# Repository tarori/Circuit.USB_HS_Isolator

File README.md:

USB 2.0 HS (480Mbps) 対応のUSBアイソレータ
* USB Type-C入力、Type-A出力
* アイソレータIC: ISOUSB211
* SN6505による低ノイズ絶縁DCDC
* 絶縁容量: <5pF (トランス次第)

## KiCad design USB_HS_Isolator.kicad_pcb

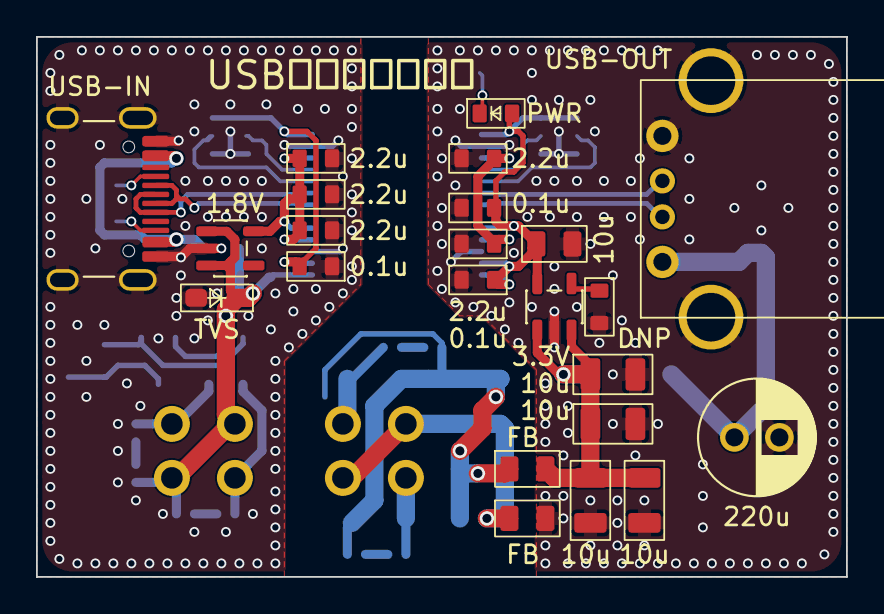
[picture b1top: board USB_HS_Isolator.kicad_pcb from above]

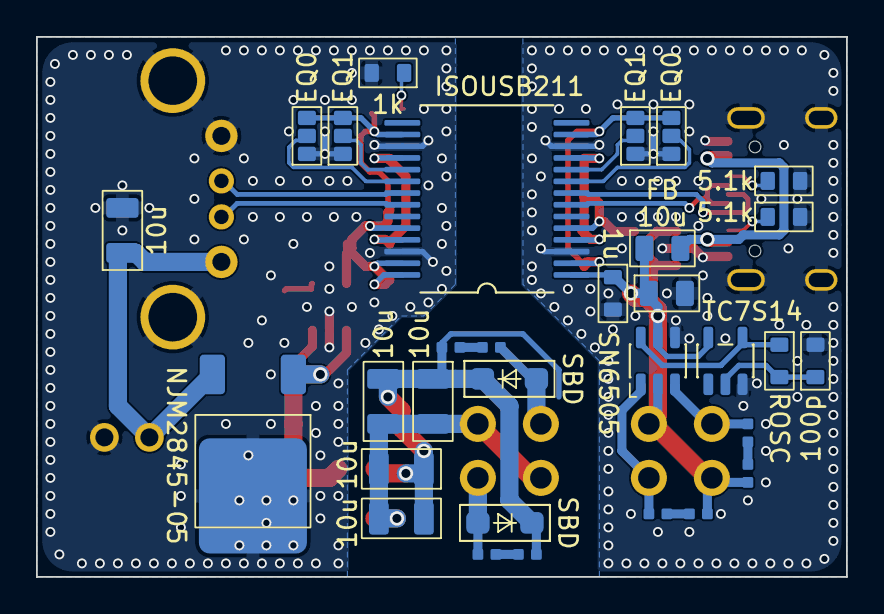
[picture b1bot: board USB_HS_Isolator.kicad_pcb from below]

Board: 4 copper layers, 45.0 x 30.0 mm, 55 parts (31 on the bottom side), 34 nets.

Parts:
C1, C4, C20: 0.1u; C_1608
C2, C3, C5, C6, C8: 2.2u; C_1608
C7: 1u; C_1608
C9, C10, C11, C12, C13, C21, C22, C23, C24: 10u; C_3216
C14, C15: 10u; C_2012
C16: 220u; CPOL_E2.5-6.3
C17: 100p; C_1608
C18, C19, C25, C26: 100p; C_1005
C27: DNP; C_1608
CON1: USB-IN; USB_C
CON2: USB-OUT; USB_A
D1, D2: SBD; D_SOD-123
D3: TVS; D_SOD-323
D4: PWR; D_1608
FB1, FB2, FB3: FB; R_2012
IC1: ISOUSB211; SSOP28-Wide
IC2: SN6505; SOT-23-6
IC3: NJM2845-05; TO-252-2
IC4: 3.3V; SOT-23-5
IC5: TC7S14; SOT-23-5
IC6: 1.8V; SOT-23-5
JP1, JP3: EQ0; R_1608J3
JP2, JP4: EQ1; R_1608J3
R1, R2: 5.1k; R_1608
R3: ROSC; R_1608
R4, R5, R6, R7: 25; R_1005
R8: 1k; R_1608
T1: Push-Pull; L_PushPull_Toroidal_12mm

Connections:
+1V8D: C2.1, C3.1, C8.1, IC1.4 (V1P8V1), IC1.5 (VCC1), IC1.11 (V1P8V1), IC6.5 (OUT)
+3V3: C4.1, C15.1, C20.1, D4.2 (A), IC1.16 (CDPENZ2), IC1.24 (VCC2), IC1.27 (V3P3V2), IC1.28 (VBUS2), IC4.5 (OUT), JP3.3 (B), JP4.3 (B)
/+3V3D: C1.2, IC1.2 (V3P3V1), IC1.13 (CDPENZ1), JP1.3 (B), JP2.3 (B)
/EQ10: IC1.9 (EQ10), JP1.2 (C)
/EQ11: IC1.10 (EQ11), JP2.2 (C)
/EQ20: IC1.20 (EQ20), JP3.2 (C)
/EQ21: IC1.19 (EQ21), JP4.2 (C)
/PGND: C9.2, C10.2, C23.2, C24.2, FB3.1, T1.5 (SB)
/USB_DD+: CON2.3 (D+), IC1.21 (DD+)
/USB_DD-: CON2.2 (D-), IC1.22 (DD-)
/USB_UD+: CON1.A6 (D+), CON1.B6 (D+), IC1.8 (UD+)
/USB_UD-: CON1.A7 (D-), CON1.B7 (D-), IC1.7 (UD-)
/VBUS1: C7.1, C14.1, C25.2, C26.2, D3.1 (K), FB1.1, IC1.1 (VBUS1), IC2.2 (VCC), IC2.5 (EN), IC5.5 (VCC), IC6.1 (IN), IC6.3 (EN), T1.2 (AB)
/VBUS2: C13.1, C16.1, CON2.1 (VBUS), IC3.3 (OUT)
DGND: C1.1, C2.2, C3.2, C7.2, C8.2, C14.2, C17.2, CON1.A1 (GND), CON1.A12 (GND), CON1.B1 (GND), CON1.B12 (GND), CON1.SH (SHIELD), D3.2 (A), IC1.3 (GND1), IC1.12 (GND1), IC2.4 (GND), IC5.3 (GND), IC6.2 (GND), JP1.1 (A), JP2.1 (A), R1.2, R2.2
GND: C4.2, C5.2, C6.2, C11.2, C12.2, C13.2, C15.2, C16.2, C20.2, C21.2, C22.2, C27.2, CON2.4 (GND), CON2.SH (Shield), FB3.2, IC1.17 (GND2), IC1.26 (GND2), IC3.2 (GND), IC4.2 (GND), JP3.1 (A), JP4.1 (A), R8.2
unnamed: C5.1, C6.1, IC1.18 (V1P8V2), IC1.25 (V1P8V2)
unnamed: C18.1, R4.2
unnamed: C19.1, R5.2
unnamed: C25.1, R6.2
unnamed: C26.1, R7.2
unnamed: CON1.A5 (CC1), R2.1
unnamed: CON1.B5 (CC2), R1.1
unnamed: CON1.A4 (VBUS), CON1.A9 (VBUS), CON1.B4 (VBUS), CON1.B9 (VBUS), FB1.2
unnamed: D1.2 (A), R4.1, T1.6 (SA)
unnamed: C9.1, C10.1, C18.2, C19.2, C23.1, C24.1, D1.1 (K), D2.1 (K), FB2.1
unnamed: D2.2 (A), R5.1, T1.4 (SC)
unnamed: D4.1 (K), R8.1
unnamed: IC2.6 (CLK), IC5.4 (YB), R3.1
unnamed: IC2.1 (D1), R7.1, T1.3 (AC)
unnamed: IC2.3 (D2), R6.1, T1.1 (AA)
unnamed: C11.1, C12.1, C21.1, C22.1, FB2.2, IC3.1 (IN), IC4.1 (IN), IC4.3 (EN)
unnamed: C27.1, IC4.4 (NP)
unnamed: C17.1, IC5.2 (A), R3.2
